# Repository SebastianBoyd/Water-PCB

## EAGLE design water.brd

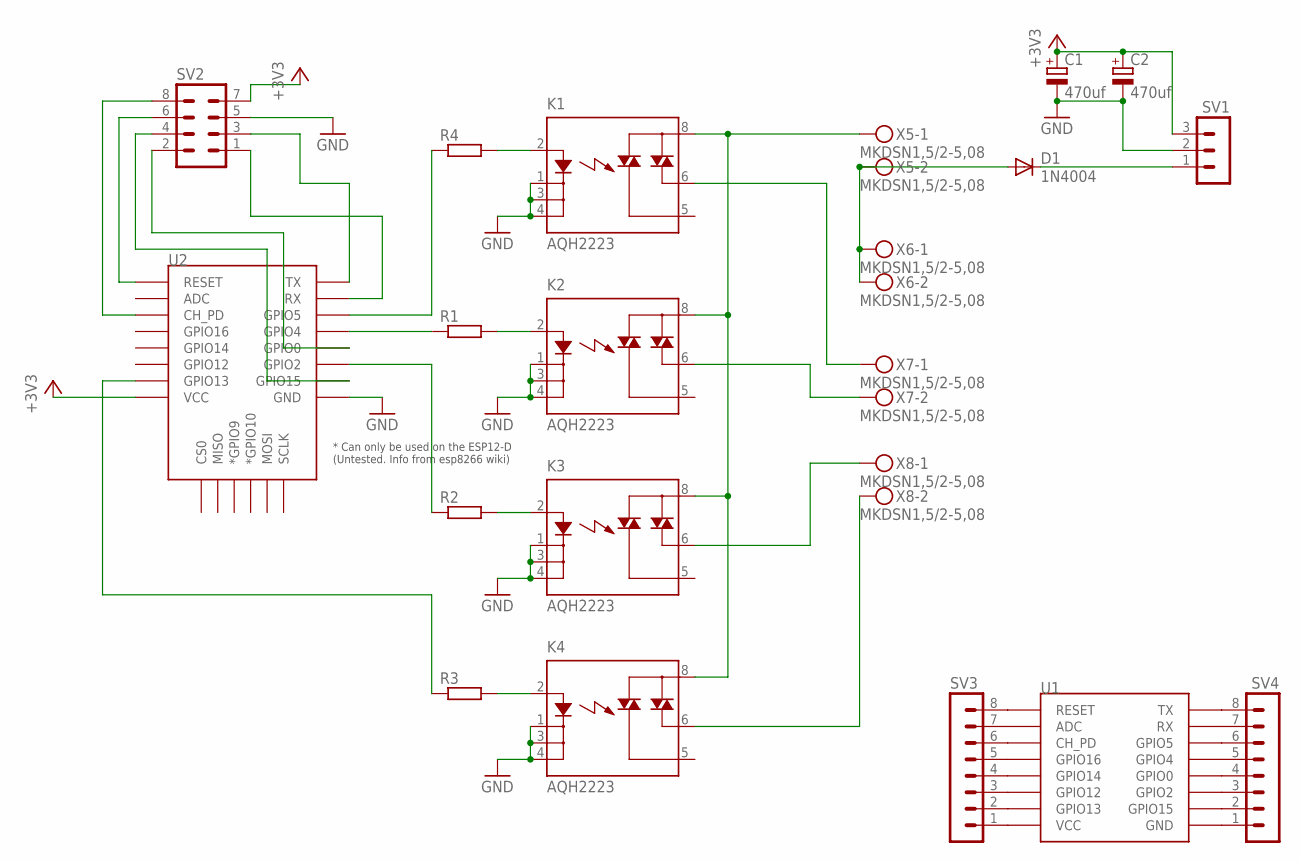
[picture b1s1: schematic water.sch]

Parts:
C1, C2: 470uf; E5-10,5
D1: 1N4004; DO41-10
K1, K2, K3, K4: AQH2223; DIL07
R1, R2, R3, R4: R-EU_R1206; R1206
SV1: MA03-1
SV2: MA04-2
SV3, SV4: MA08-1
U1: ESP12EPOGO; ESP12E-POGO
U2: ESP12ESMD; ESP12E-SMD
X5, X6, X7, X8: MKDSN1,5/2-5,08

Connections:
+3V3: C1.+, C2.+, SV1.3, SV2.7, U2.VCC
GND: C1.-, C2.-, K1.1 (K), K1.3 (K1), K1.4 (K2), K2.1 (K), K2.3 (K1), K2.4 (K2), K3.1 (K), K3.3 (K1), K3.4 (K2), K4.1 (K), K4.3 (K1), K4.4 (K2), SV1.2, SV2.5, U2.GND
unnamed: K1.2 (A), R4.2
unnamed: K2.2 (A), R1.2
unnamed: K3.2 (A), R2.2
unnamed: K4.2 (A), R3.2
unnamed: R4.1, U2.GPIO5
unnamed: R1.1, U2.GPIO4
unnamed: R2.1, U2.GPIO2
unnamed: R3.1, U2.GPIO13
unnamed: K4.6 (DS3), X8.2
unnamed: K3.6 (DS3), X8.1
unnamed: K2.6 (DS3), X7.2
unnamed: K1.6 (DS3), X7.1
unnamed: SV2.8, U2.CH_PD
unnamed: D1.C, SV1.1
unnamed: D1.A, X5.2, X6.1, X6.2
unnamed: SV2.6, U2.RESET
unnamed: SV2.3, U2.TXD0 (TX)
unnamed: SV2.1, U2.RXD0 (RX)
unnamed: SV2.4, U2.GPIO15
unnamed: SV2.2, U2.GPIO0
unnamed: K1.8 (DS1), K2.8 (DS1), K3.8 (DS1), K4.8 (DS1), X5.1
unnamed: SV3.1, U1.VCC
unnamed: SV3.2, U1.GPIO13
unnamed: SV3.3, U1.GPIO12
unnamed: SV3.4, U1.GPIO14
unnamed: SV3.5, U1.GPIO16
unnamed: SV3.6, U1.CH_PD
unnamed: SV3.7, U1.ADC
unnamed: SV3.8, U1.RESET
unnamed: SV4.1, U1.GND
unnamed: SV4.2, U1.GPIO15
unnamed: SV4.3, U1.GPIO2
unnamed: SV4.4, U1.GPIO0
unnamed: SV4.5, U1.GPIO4
unnamed: SV4.6, U1.GPIO5
unnamed: SV4.7, U1.RXD0 (RX)
unnamed: SV4.8, U1.TXD0 (TX)

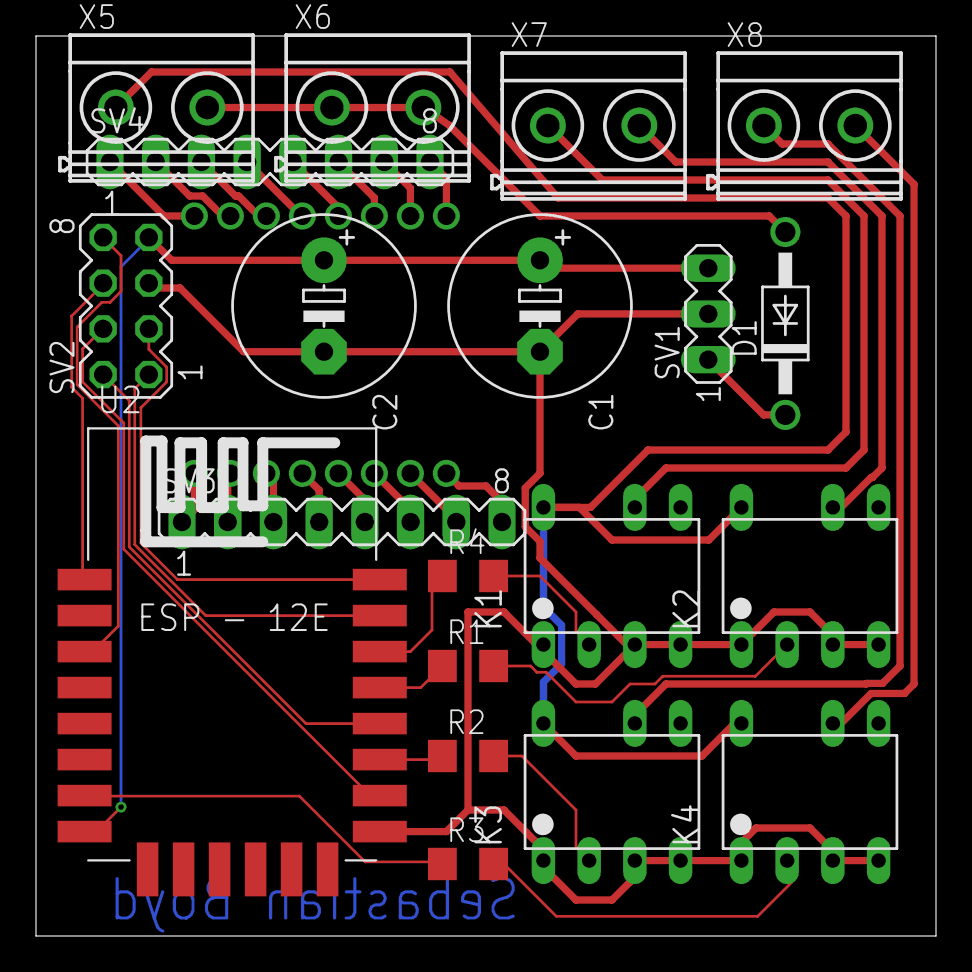
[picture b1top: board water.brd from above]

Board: 2 copper layers, 50.0 x 50.0 mm, 21 parts (1 on the bottom side), 39 nets.

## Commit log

2016-12-14 Add kicad file
2017-05-13 Remove kicad
2017-05-13 Start in eagle
2017-05-13 Move parts
2017-05-16 Restart routing
2017-05-16 Add capacitors
2017-05-16 Add led
2017-05-17 Add custom part
2017-05-17 Add pogo test bed
2017-05-17 More features
2017-05-17 Add bottom pour
2017-05-18 Add design rules and export config
2017-05-18 Fix conflicts
2017-05-18 revert to where it worked
2017-05-19 Finalize
